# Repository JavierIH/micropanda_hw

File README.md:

# micropanda_hw
Micropanda's hardware sources and gerbers

Licensed under CC BY-SA 3.0

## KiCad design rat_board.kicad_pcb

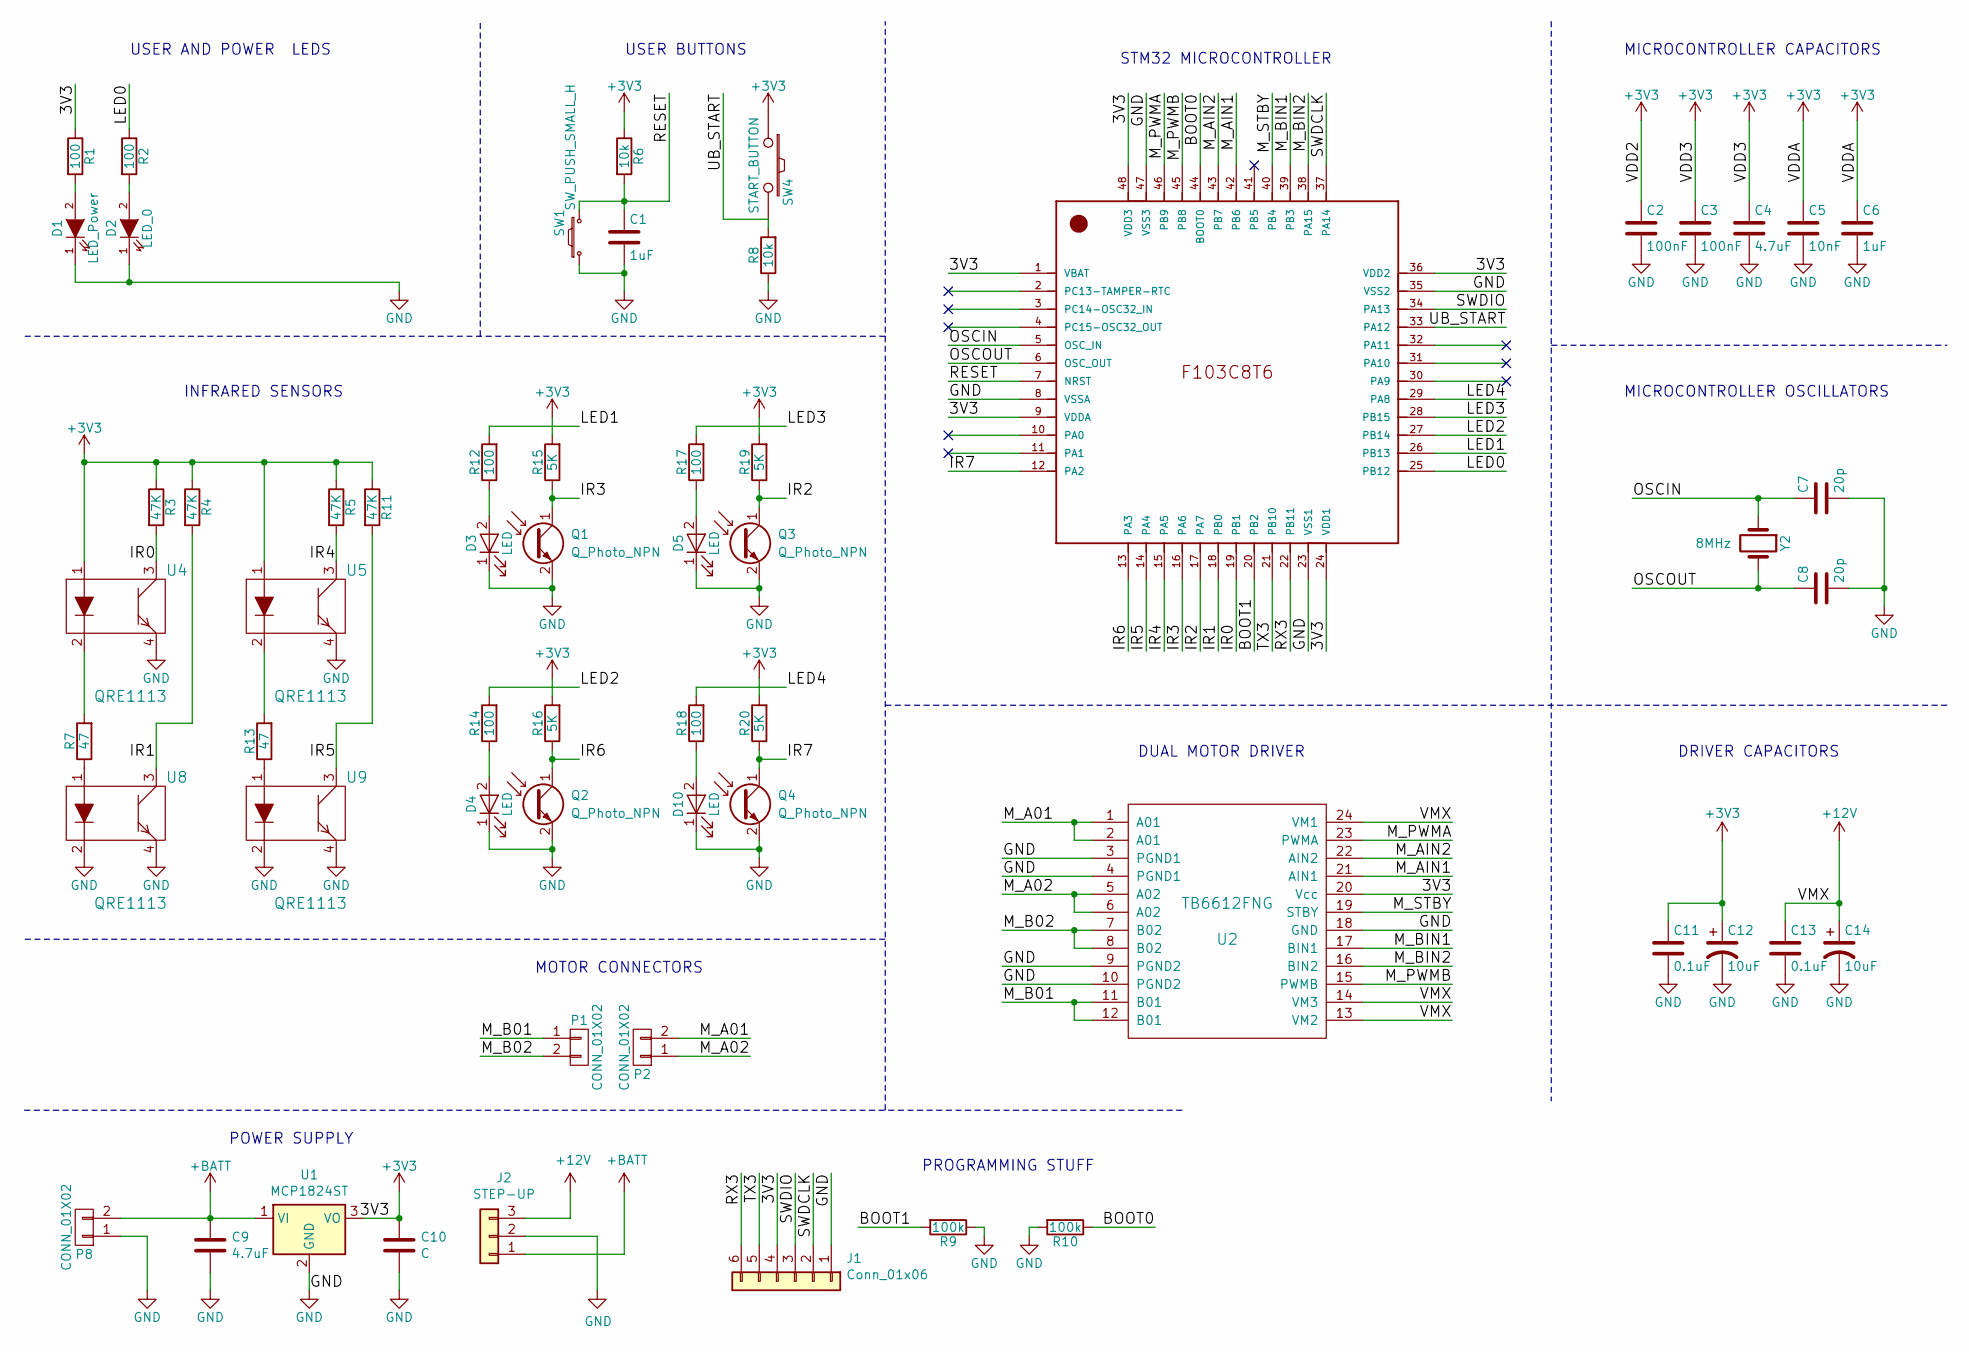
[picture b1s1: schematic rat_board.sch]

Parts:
C1, C6: 1uF; R_0603_HandSoldering
C2, C3: 100nF; R_0603_HandSoldering
C4, C9: 4.7uF; R_0603_HandSoldering
C5: 10nF; R_0603_HandSoldering
C7, C8: 20p; R_0603_HandSoldering
C10: C; R_0603_HandSoldering
C11, C13: 0.1uF; R_0603_HandSoldering
C12, C14: 10uF; SMD-1206_Pol
D1: LED_Power; LED_0603
D2: LED_0; LED_0603
D3, D4, D5, D10: LED; LED_D3.0mm_Horizontal_O1.27mm_Z2.0mm
J1: Conn_01x06; Pin_Header_Straight_1x06_Pitch2.54mm
J2: STEP-UP; Pin_Header_Straight_1x03_Pitch2.54mm
P1, P2, P8: CONN_01X02; Pin_Header_Straight_1x02_Pitch2.54mm
Q1, Q2, Q3, Q4: Q_Photo_NPN; LED_D3.0mm_Horizontal_O1.27mm_Z2.0mm
R1, R2, R12, R14, R17, R18: 100; R_0603_HandSoldering
R3, R4, R5, R11: 47K; R_0603_HandSoldering
R6, R8: 10k; R_0603_HandSoldering
R7, R13: 47; R_0603_HandSoldering
R9, R10: 100k; R_0603_HandSoldering
R15, R16, R19, R20: 5K; R_0603_HandSoldering
SW1: SW_PUSH_SMALL_H; SW_SPST_B3U-1000P
SW4: START_BUTTON; SW_SPST_B3U-1000P
U1: MCP1824ST; SOT-223-3_TabPin2
U2: TB6612FNG; driver_tuneado
U3: STM32F103C8T6; LQFP-48_7x7mm_Pitch0.5mm
U4, U5, U8, U9: QRE1113; QRE1113GR
Y2: 8MHz; Crystal_HC50-U_Vertical

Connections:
+3V3: C2.1, C3.1, C4.1, C5.1, C6.1, C10.1, C11.1, C12.1, J1.4, R1.1, R3.1, R4.1, R5.1, R6.1, R11.1, R15.2, R16.2, R19.2, R20.2, SW4.1, U1.3 (VO), U2.20 (Vcc), U3.1 (VBAT), U3.9 (VDDA), U3.24 (VDD1), U3.36 (VDD2), U3.48 (VDD3), U4.1, U5.1
+12V: C13.1, C14.1, J2.3, U2.13 (VM2), U2.14 (VM3), U2.24 (VM1)
+BATT: C9.1, J2.1, P8.2, U1.1 (VI)
/BOOT0: R10.1, U3.44 (BOOT0)
/BOOT1: R9.2, U3.20 (PB2)
/IR0: R3.2, U3.19 (PB1), U4.3
/IR1: R4.2, U3.18 (PB0), U8.3
/IR2: Q3.1 (C), R19.1, U3.17 (PA7)
/IR3: Q1.1 (C), R15.1, U3.16 (PA6)
/IR4: R5.2, U3.15 (PA5), U5.3
/IR5: R11.2, U3.14 (PA4), U9.3
/IR6: Q2.1 (C), R16.1, U3.13 (PA3)
/IR7: Q4.1 (C), R20.1, U3.12 (PA2)
/LED0: R2.1, U3.25 (PB12)
/LED1: R12.2, U3.26 (PB13)
/LED2: R14.2, U3.27 (PB14)
/LED3: R17.2, U3.28 (PB15)
/LED4: R18.2, U3.29 (PA8)
/M_A01: P2.2, U2.1 (A01), U2.2 (A01)
/M_A02: P2.1, U2.5 (A02), U2.6 (A02)
/M_AIN1: U2.21 (AIN1), U3.42 (PB6)
/M_AIN2: U2.22 (AIN2), U3.43 (PB7)
/M_B01: P1.1, U2.11 (B01), U2.12 (B01)
/M_B02: P1.2, U2.7 (B02), U2.8 (B02)
/M_BIN1: U2.17 (BIN1), U3.39 (PB3)
/M_BIN2: U2.16 (BIN2), U3.38 (PA15)
/M_PWMA: U2.23 (PWMA), U3.46 (PB9)
/M_PWMB: U2.15 (PWMB), U3.45 (PB8)
/M_STBY: U2.19 (STBY), U3.40 (PB4)
/OSCIN: C7.1, U3.5 (OSC_IN), Y2.1
/OSCOUT: C8.1, U3.6 (OSC_OUT), Y2.2
/RESET: C1.1, R6.2, SW1.2, U3.7 (NRST)
/RX3: J1.6, U3.22 (PB11)
/SWDCLK: J1.2, U3.37 (PA14)
/SWDIO: J1.3, U3.34 (PA13)
/TX3: J1.5, U3.21 (PB10)
/UB_START: R8.2, SW4.2, U3.33 (PA12)
GND: C1.2, C2.2, C3.2, C4.2, C5.2, C6.2, C7.2, C8.2, C9.2, C10.2, C11.2, C12.2, C13.2, C14.2, D1.1 (K), D2.1 (K), D3.1 (K), D4.1 (K), D5.1 (K), D10.1 (K), J1.1, J2.2, P8.1, Q1.2 (E), Q2.2 (E), Q3.2 (E), Q4.2 (E), R8.1, R9.1, R10.2, SW1.1, U1.2 (GND), U2.3 (PGND1), U2.4 (PGND1), U2.9 (PGND2), U2.10 (PGND2), U2.18 (GND), U3.8 (VSSA), U3.23 (VSS1), U3.35 (VSS2), U3.47 (VSS3), U4.4, U5.4, U8.2, U8.4, U9.2, U9.4
unnamed: D1.2 (A), R1.2
unnamed: D2.2 (A), R2.2
unnamed: D3.2 (A), R12.1
unnamed: D4.2 (A), R14.1
unnamed: D5.2 (A), R17.1
unnamed: D10.2 (A), R18.1
unnamed: R7.1, U8.1
unnamed: R7.2, U4.2
unnamed: R13.1, U9.1
unnamed: R13.2, U5.2

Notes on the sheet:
MICROCONTROLLER CAPACITORS
DRIVER CAPACITORS
MICROCONTROLLER OSCILLATORS
DUAL MOTOR DRIVER
STM32 MICROCONTROLLER
USER AND POWER LEDS
MOTOR CONNECTORS
PROGRAMMING STUFF
POWER SUPPLY
USER BUTTONS
INFRARED SENSORS

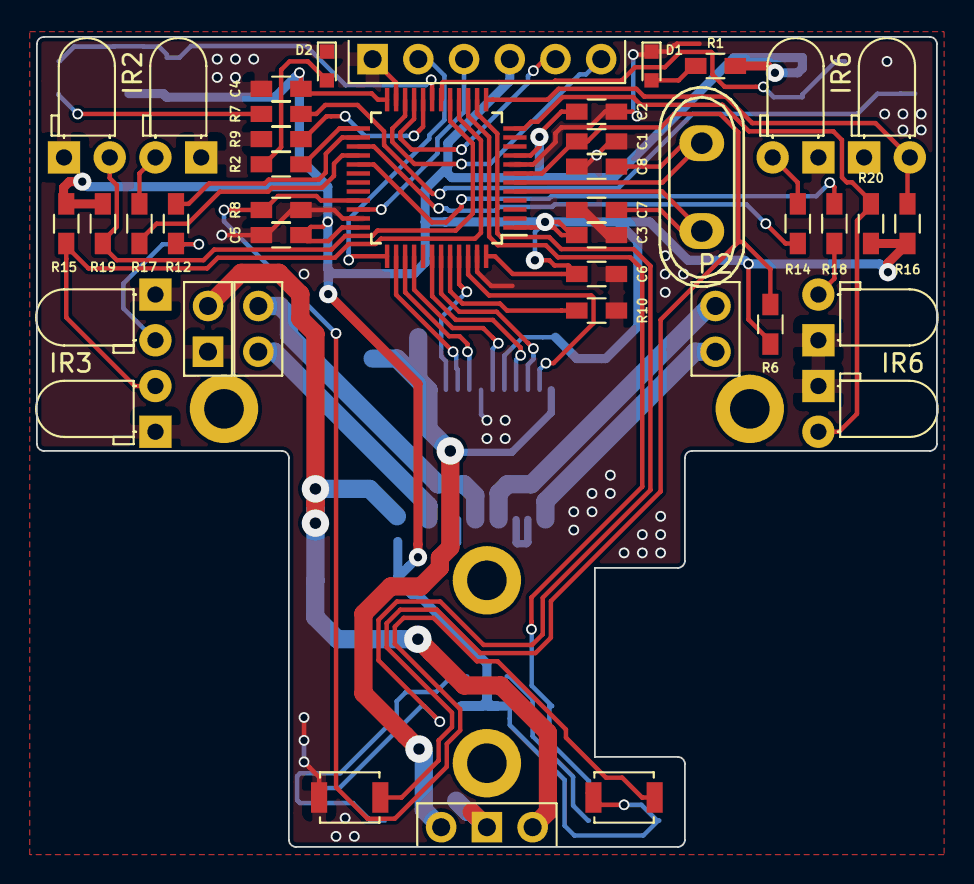
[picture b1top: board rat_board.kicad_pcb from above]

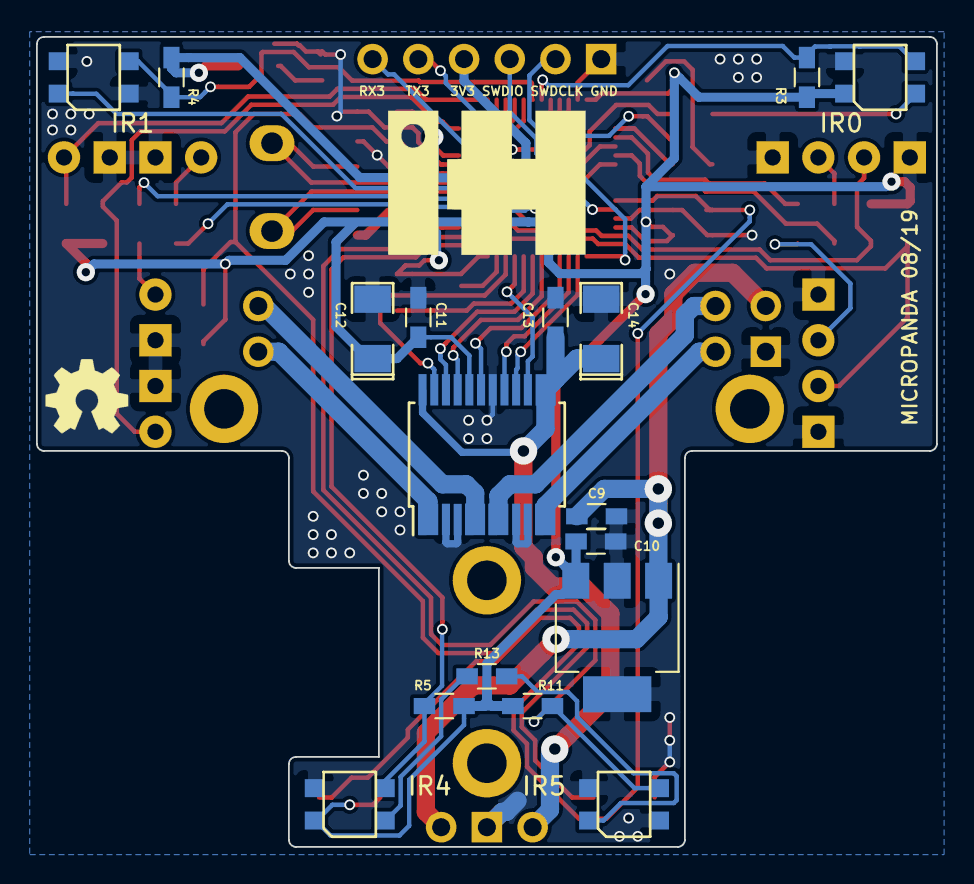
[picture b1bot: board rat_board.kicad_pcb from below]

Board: 2 copper layers, 50.0 x 45.0 mm, 59 parts (17 on the bottom side), 48 nets.

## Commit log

2019-10-13 hardware sources and gerbers
